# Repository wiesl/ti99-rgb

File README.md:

TMS9929A RGB Converter
======================

This RGB converter is based on this great project:
[TMS9929A RGB and Component adapter - A high resolution Component, RGB or SCART adapter for MSX and Colecovision](https://hackaday.io/project/13056-tms9929a-rgb-and-component-adapter).

It converts signals from a TMS9929 with correct colors to RGB.

See also this [thread](https://www.classic-computers.org.nz/forums/viewtopic.php?f=11&t=960) for more information.

Authors
=======

Original author: Copyright 2016: Alexis Kotlowy <256byteram@gmail.com>

Enhanced version: Copyright 2017: Gerhard Wiesinger <ti99@wiesinger.com>

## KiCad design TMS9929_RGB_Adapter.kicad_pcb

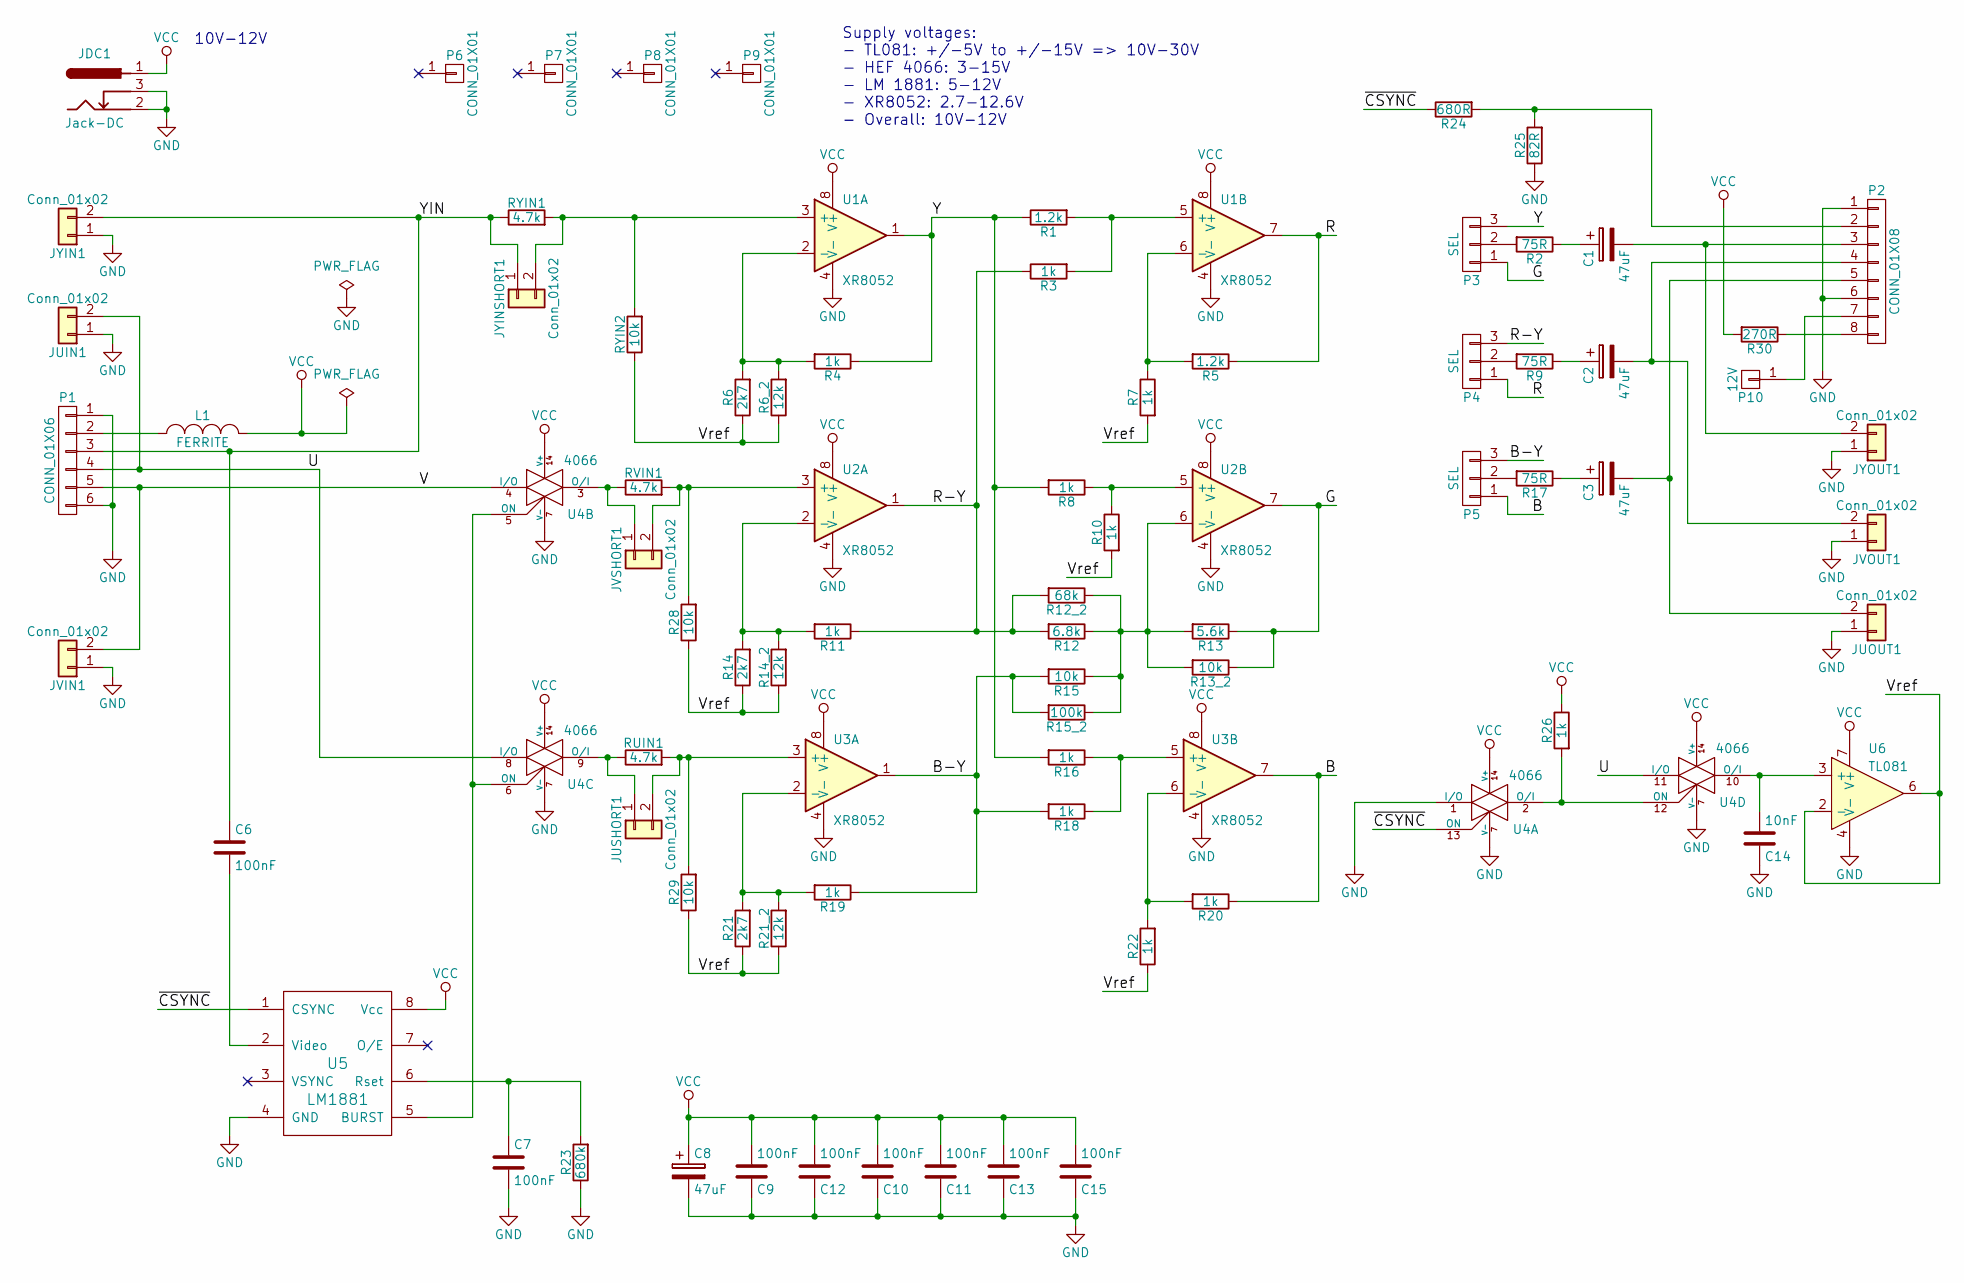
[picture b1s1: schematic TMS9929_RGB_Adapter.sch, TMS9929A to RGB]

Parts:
C1, C2, C3, C8: 47uF; TantalC_SizeB_EIA-3528_HandSoldering
C6, C7, C9, C10, C11, C12, C13, C15: 100nF; C_0805_HandSoldering
C14: 10nF; C_0805_HandSoldering
JDC1: Jack-DC; jack_2mm
JUIN1: Conn_01x02; rca_white
JUOUT1: Conn_01x02; rca_white
JUSHORT1: Conn_01x02; Pin_Header_Straight_1x02_Pitch2.54mm
JVIN1: Conn_01x02; rca_red
JVOUT1: Conn_01x02; rca_red
JVSHORT1: Conn_01x02; Pin_Header_Straight_1x02_Pitch2.54mm
JYIN1: Conn_01x02; rca_black
JYINSHORT1: Conn_01x02; Pin_Header_Straight_1x02_Pitch2.54mm
JYOUT1: Conn_01x02; rca_black
L1: FERRITE; R_1206_HandSoldering
P1: CONN_01X06; Pin_Header_Straight_1x06_Pitch2.54mm
P2: CONN_01X08; Pin_Header_Straight_1x08_Pitch2.54mm
P3, P4, P5: SEL; Pin_Header_Straight_1x03_Pitch2.54mm
P6, P7, P8, P9: CONN_01X01; 1pin
P10: 12V; Pin_Header_Straight_1x01
R1, R5: 1.2k; R_0805_HandSoldering
R2, R9, R17: 75R; R_0805_HandSoldering
R3, R4, R7, R8, R10, R11, R16, R18, R19, R20, R22, R26: 1k; R_0805_HandSoldering
R6, R14, R21: 2k7; R_0805_HandSoldering
R6_2, R14_2, R21_2: 12k; R_0805_HandSoldering
R12: 6.8k; R_0805_HandSoldering
R12_2: 68k; R_0805_HandSoldering
R13: 5.6k; R_0805_HandSoldering
R13_2, R15, R28, R29: 10k; R_0805_HandSoldering
R15_2: 100k; R_0805_HandSoldering
R23: 680k; R_0805_HandSoldering
R24: 680R; R_0805_HandSoldering
R25: 82R; R_0805_HandSoldering
R30: 270R; R_0805_HandSoldering
RUIN1: 4.7k; R_0805_HandSoldering
RVIN1: 4.7k; R_0805_HandSoldering
RYIN1: 4.7k; R_0805_HandSoldering
RYIN2: 10k; R_0805_HandSoldering
U1, U2, U3: XR8052; SOIC-8-N
U4: 4066; SOIC-14_N
U5: LM1881; SOIC-8-N
U6: TL081; SOIC-8-N

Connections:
/B: P5.1, R20.1, U3.7
/B-Y: P5.3, R15.2, R15_2.2, R18.2, R19.1, U3.1
/G: P3.1, R13.1, R13_2.1, U2.7
/R: P4.1, R5.1, U1.7
/R-Y: P4.3, R3.1, R11.1, R12.2, R12_2.2, U2.1
/U: JUIN1.2, P1.4, U4.8 (I/O), U4.11 (I/O)
/V: JVIN1.2, P1.5, U4.4 (I/O)
/Vref: R6.1, R6_2.1, R7.2, R10.2, R14.1, R14_2.1, R21.1, R21_2.1, R22.1, R28.1, R29.1, RYIN2.1, U6.2 (-), U6.6
/Y: P3.3, R1.1, R4.1, R8.2, R16.2, U1.1
/YIN: C6.1, JYIN1.2, JYINSHORT1.1, P1.3, RYIN1.1
/~CSYNC: R24.1, U4.13 (ON), U5.1 (CSYNC)
GND: C7.2, C8.2, C9.1, C10.1, C11.1, C12.1, C13.1, C14.1, C15.1, JDC1.2, JDC1.3, JUIN1.1, JUOUT1.1, JVIN1.1, JVOUT1.1, JYIN1.1, JYOUT1.1, P1.1, P1.6, P2.1, P2.6, R23.1, R25.1, U1.4 (V-), U2.4 (V-), U3.4 (V-), U4.1 (I/O), U4.7 (V-), U5.4 (GND), U6.4 (V-)
unnamed: C1.1, R2.1
unnamed: C1.2, JYOUT1.2, P2.3
unnamed: C2.1, R9.1
unnamed: C2.2, JVOUT1.2, P2.4
unnamed: C3.1, R17.1
unnamed: C3.2, JUOUT1.2, P2.5
unnamed: C6.2, U5.2 (Video)
unnamed: C7.1, R23.2, U5.6 (Rset)
unnamed: C14.2, U4.10 (O/I), U6.3 (+)
unnamed: JUSHORT1.1, RUIN1.1, U4.9 (O/I)
unnamed: JUSHORT1.2, R29.2, RUIN1.2, U3.3 (+)
unnamed: JVSHORT1.1, RVIN1.1, U4.3 (O/I)
unnamed: JVSHORT1.2, R28.2, RVIN1.2, U2.3 (+)
unnamed: JYINSHORT1.2, RYIN1.2, RYIN2.2, U1.3 (+)
unnamed: L1.1, P1.2
unnamed: P2.2, R24.2, R25.2
unnamed: P2.8, R30.1
unnamed: P3.2, R2.2
unnamed: P4.2, R9.2
unnamed: P5.2, R17.2
unnamed: P2.7, P10.1
unnamed: R1.2, R3.2, U1.5 (+)
unnamed: R4.2, R6.2, R6_2.2, U1.2 (-)
unnamed: R5.2, R7.1, U1.6 (-)
unnamed: R8.1, R10.1, U2.5 (+)
unnamed: R11.2, R14.2, R14_2.2, U2.2 (-)
unnamed: R12.1, R12_2.1, R13.2, R13_2.2, R15.1, R15_2.1, U2.6 (-)
unnamed: R16.1, R18.1, U3.5 (+)
unnamed: R19.2, R21.2, R21_2.2, U3.2 (-)
unnamed: R20.2, R22.2, U3.6 (-)
unnamed: R26.2, U4.2 (O/I), U4.12 (ON)
unnamed: U4.5 (ON), U4.6 (ON), U5.5 (BURST)
VCC: C8.1, C9.2, C10.2, C11.2, C12.2, C13.2, C15.2, JDC1.1, L1.2, R26.1, R30.2, U1.8 (V+), U2.8 (V+), U3.8 (V+), U4.14 (V+), U5.8 (Vcc), U6.7 (V+)

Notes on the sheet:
10V-12V
Supply voltages: - TL081: +/-5V to +/-15V => 10V-30V - HEF 4066: 3-15V - LM 1881: 5-12V - XR8052: 2.7-12.6V - Overall: 10V-12V

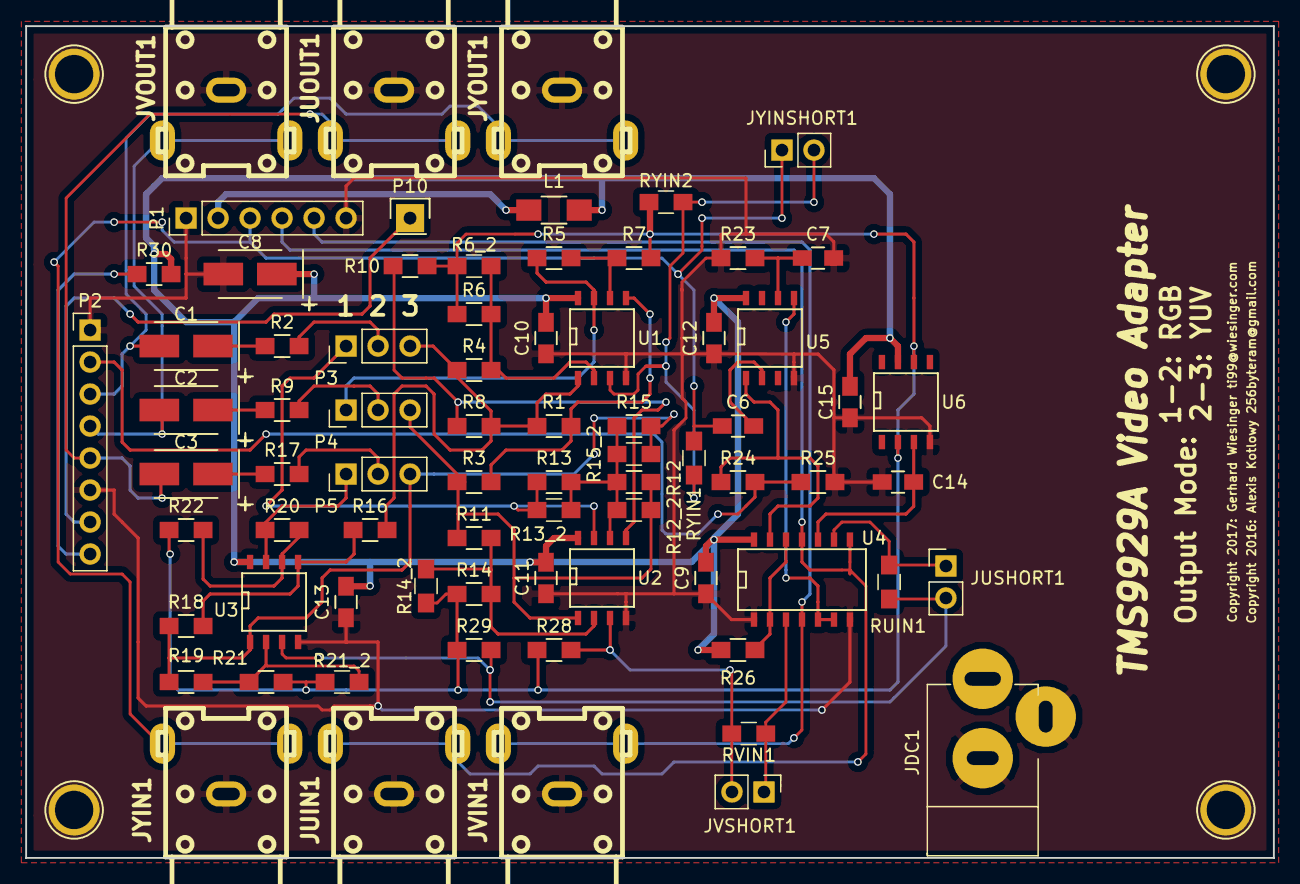
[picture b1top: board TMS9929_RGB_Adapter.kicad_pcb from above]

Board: 2 copper layers, 99.1 x 66.0 mm, 79 parts (0 on the bottom side), 45 nets.

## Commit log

2017-08-14 Initial import
2017-09-17 Initial changes to new version, copyright, DRC, etc.
2017-09-17 Updated libraries and removed old drill report file
2017-09-17 Updated schematic & PCB for added Cinch connectors as well as power supply connector and damping resistors/jumpers
2017-09-17 Corrected silkscreen with masks (moved it)
2017-09-19 Show copper layers
2017-09-19 Remove *.drl file
2017-09-19 Smaller PCB cosmetics
2017-09-24 schematic: Added comments for power supply, moved capacitor at TL081 (cosmetics)
2017-09-24 Added new resistors in parallel to existing ones to solder standard resistor values
2019-06-02 Updated .gitignore
2019-06-02 Added README.md
